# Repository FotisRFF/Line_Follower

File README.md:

##LINE FOLLOWER BODY 3D VIEW

##LINE FOLLOWER SENSOR 3D VIEW

#FRONT 

#BACK

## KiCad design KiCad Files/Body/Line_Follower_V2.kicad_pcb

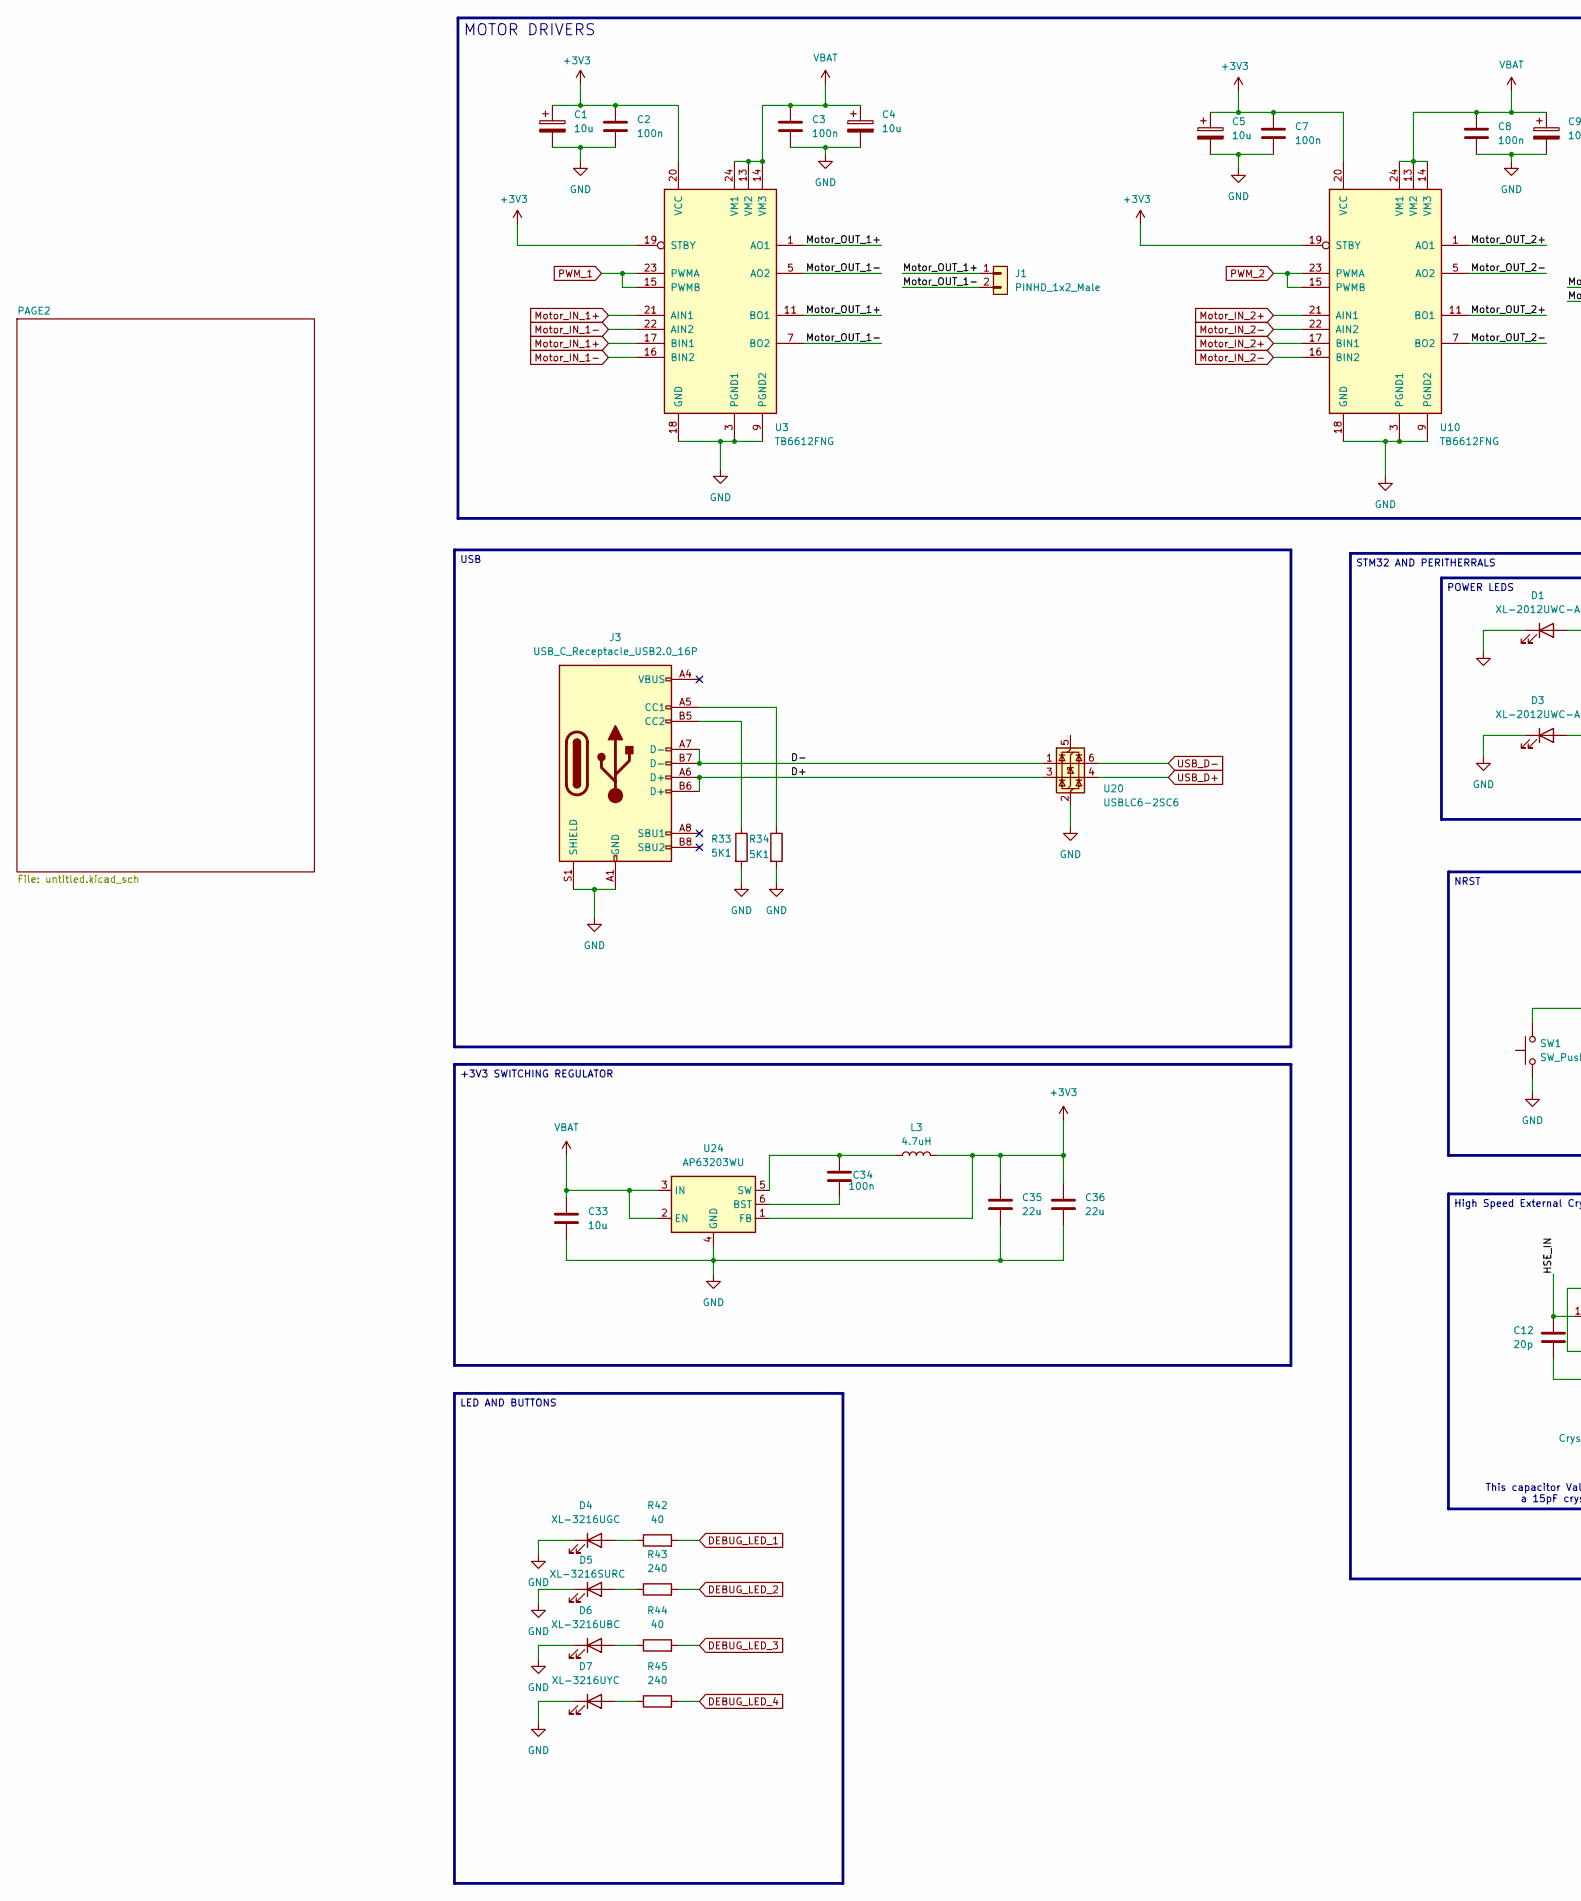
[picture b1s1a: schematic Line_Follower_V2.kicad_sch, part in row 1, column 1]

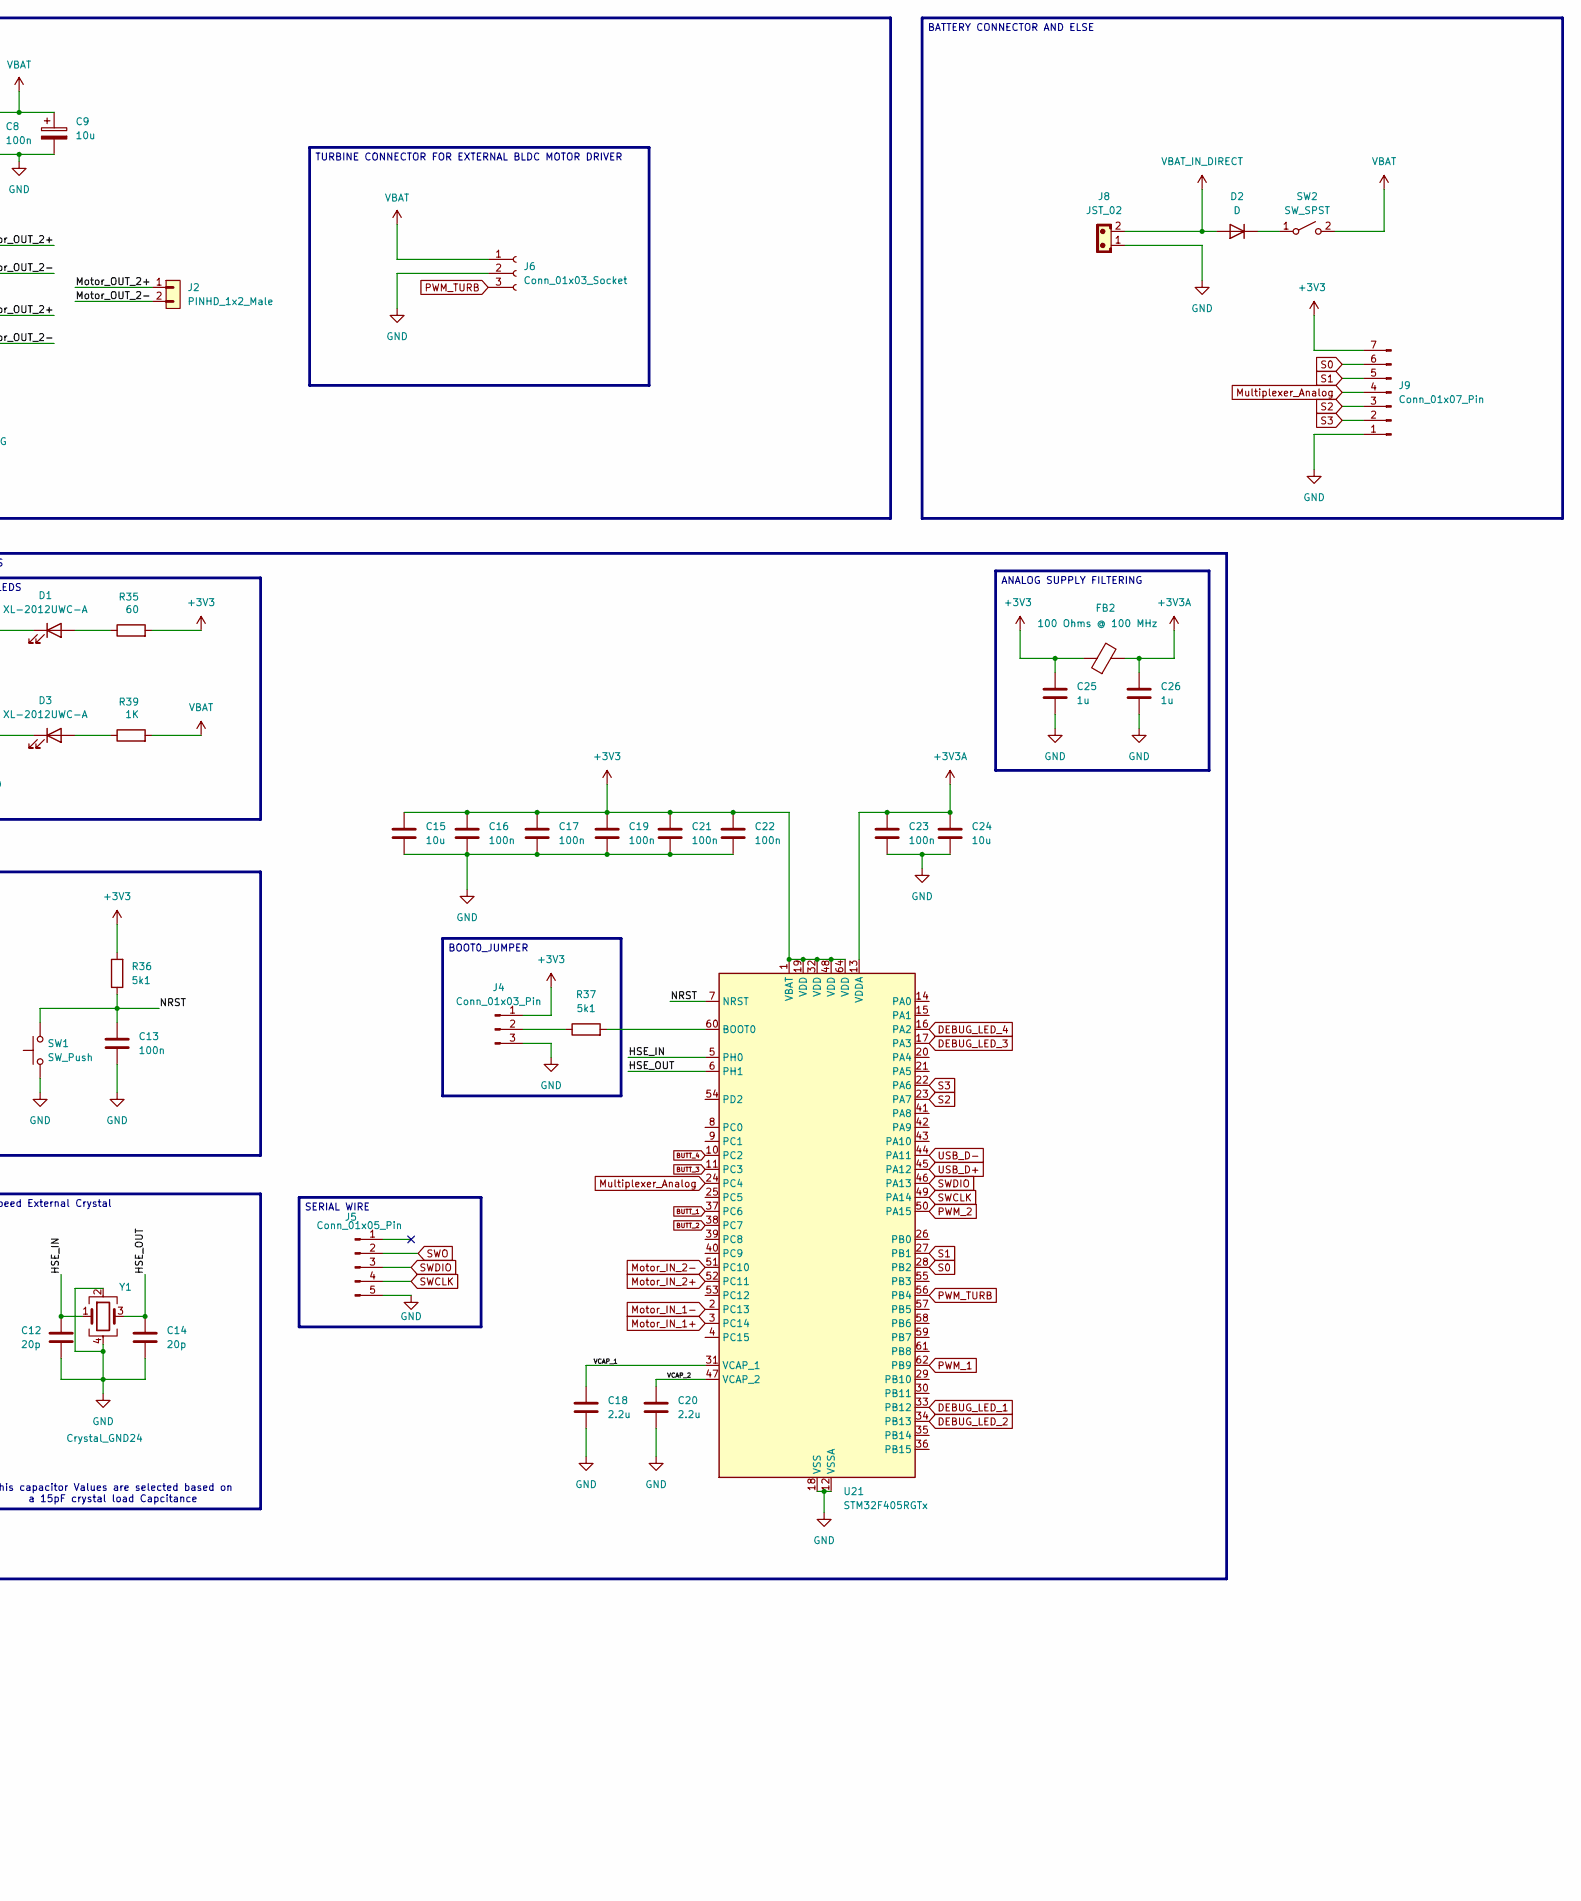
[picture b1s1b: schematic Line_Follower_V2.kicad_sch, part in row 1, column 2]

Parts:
C1, C4, C5, C9: 10u; CP_EIA-1608-08_AVX-J_HandSolder
C2, C3, C7, C8: 100n; C_0805_2012Metric
C12, C14: 20p; C_0402_1005Metric_Pad0.74x0.62mm_HandSolder
C13: 100n; C_0805_2012Metric_Pad1.18x1.45mm_HandSolder
C15, C24: 10u; C_0805_2012Metric_Pad1.18x1.45mm_HandSolder
C16, C17, C19, C21, C22, C23, C34: 100n; C_0402_1005Metric_Pad0.74x0.62mm_HandSolder
C18, C20: 2.2u; C_0603_1608Metric
C25, C26: 1u; C_0603_1608Metric
C33: 10u; C_0805_2012Metric
C35, C36: 22u; C_0805_2012Metric
D1, D3: XL-2012UWC-A; LED_0805_2012Metric_Pad1.15x1.40mm_HandSolder
D2: D; D_1206_3216Metric_Pad1.42x1.75mm_HandSolder
D4: XL-3216UGC; LED_1206_3216Metric
D5: XL-3216SURC; LED_1206_3216Metric
D6: XL-3216UBC; LED_1206_3216Metric
D7: XL-3216UYC; LED_1206_3216Metric
FB2: 100 Ohms @ 100 MHz; L_0805_2012Metric
J1, J2: PINHD_1x2_Male; PinHeader_1x02_P2.54mm_Vertical
J3: USB_C_Receptacle_USB2.0_16P; USB_C_Receptacle_GCT_USB4105-xx-A_16P_TopMnt_Horizontal
J4: Conn_01x03_Pin; PinHeader_1x03_P2.54mm_Vertical
J5: Conn_01x05_Pin; PinHeader_1x05_P2.54mm_Vertical
J6: Conn_01x03_Socket; PinHeader_1x03_P2.54mm_Vertical
J8: JST_02; JST_EH_B2B-EH-A_1x02_P2.50mm_Vertical
J9: Conn_01x07_Pin; PinHeader_1x07_P2.54mm_Vertical
L3: 4.7uH; L_Sunlord_MWSA0402S
R33, R34: 5K1; R_0805_2012Metric_Pad1.20x1.40mm_HandSolder
R35: 60; R_0805_2012Metric
R36, R37: 5k1; R_0805_2012Metric_Pad1.20x1.40mm_HandSolder
R39: 1K; R_0805_2012Metric
R42, R44: 40; R_0805_2012Metric_Pad1.20x1.40mm_HandSolder
R43, R45: 240; R_0805_2012Metric_Pad1.20x1.40mm_HandSolder
SW1: SW_Push; SW_PUSH_6mm_H13mm
SW2: SW_SPST; SW_DIP_SPSTx01_Slide_6.7x4.1mm_W7.62mm_P2.54mm_LowProfile
U3, U10: TB6612FNG; SSOP-24_5.3x8.2mm_P0.65mm
U20: USBLC6-2SC6; SOT-23-6
U21: STM32F405RGTx; LQFP-64_10x10mm_P0.5mm
U24: AP63203WU; TSOT-23-6
Y1: Crystal_GND24; Crystal_SMD_3225-4Pin_3.2x2.5mm

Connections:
+3V3: C1.1, C2.1, C5.1, C7.1, C15.1, C16.1, C17.1, C19.1, C21.1, C22.1, C25.1, C35.1, C36.1, FB2.1, J4.1, J9.7, L3.2, R35.2, R36.2, U3.19 (STBY), U3.20 (VCC), U10.19 (STBY), U10.20 (VCC), U21.1 (VBAT), U21.19 (VDD), U21.32 (VDD), U21.48 (VDD), U21.64 (VDD), U24.1 (FB)
+3V3A: C23.1, C24.1, C26.1, FB2.2, U21.13 (VDDA)
/D+: J3.A6 (D+), J3.B6 (D+), U20.3 (I/O2)
/D-: J3.A7 (D-), J3.B7 (D-), U20.1 (I/O1)
/HSE_IN: C12.1, U21.5 (PH0), Y1.1
/HSE_OUT: C14.1, U21.6 (PH1), Y1.3
/Motor_OUT_1+: J1.1, U3.1 (AO1), U3.2 (AO1), U3.11 (BO1), U3.12 (BO1)
/Motor_OUT_1-: J1.2, U3.5 (AO2), U3.6 (AO2), U3.7 (BO2), U3.8 (BO2)
/Motor_OUT_2+: J2.1, U10.1 (AO1), U10.2 (AO1), U10.11 (BO1), U10.12 (BO1)
/Motor_OUT_2-: J2.2, U10.5 (AO2), U10.6 (AO2), U10.7 (BO2), U10.8 (BO2)
/NRST: C13.1, R36.1, SW1.2, U21.7 (NRST)
/VCAP_1: C18.1, U21.31 (VCAP_1)
/VCAP_2: C20.1, U21.47 (VCAP_2)
BUTT_1: U21.37 (PC6)
BUTT_2: U21.38 (PC7)
BUTT_3: U21.11 (PC3)
BUTT_4: U21.10 (PC2)
DEBUG_LED_1: R42.2, U21.33 (PB12)
DEBUG_LED_2: R43.2, U21.34 (PB13)
DEBUG_LED_3: R44.2, U21.17 (PA3)
DEBUG_LED_4: R45.2, U21.16 (PA2)
GND: C1.2, C2.2, C3.2, C4.2, C5.2, C7.2, C8.2, C9.2, C12.2, C13.2, C14.2, C15.2, C16.2, C17.2, C18.2, C19.2, C20.2, C21.2, C22.2, C23.2, C24.2, C25.2, C26.2, C33.2, C35.2, C36.2, D1.1 (K), D3.1 (K), D4.1 (K), D5.1 (K), D6.1 (K), D7.1 (K), J3.A1 (GND), J3.A12 (GND), J3.B1 (GND), J3.B12 (GND), J3.S1 (SHIELD), J4.3, J5.5, J6.2, J8.1, J9.1, R33.2, R34.2, SW1.1, U3.3 (PGND1), U3.4 (PGND1), U3.9 (PGND2), U3.10 (PGND2), U3.18 (GND), U10.3 (PGND1), U10.4 (PGND1), U10.9 (PGND2), U10.10 (PGND2), U10.18 (GND), U20.2 (GND), U21.12 (VSSA), U21.18 (VSS), U21.63 (VSS), U24.4 (GND), Y1.2, Y1.4
Motor_IN_1+: U3.17 (BIN1), U3.21 (AIN1), U21.3 (PC14)
Motor_IN_1-: U3.16 (BIN2), U3.22 (AIN2), U21.2 (PC13)
Motor_IN_2+: U10.17 (BIN1), U10.21 (AIN1), U21.52 (PC11)
Motor_IN_2-: U10.16 (BIN2), U10.22 (AIN2), U21.51 (PC10)
Multiplexer_Analog: J9.4, U21.24 (PC4)
unnamed: D1.2 (A), R35.1
unnamed: D2.1 (K), SW2.1 (A)
unnamed: D3.2 (A), R39.1
unnamed: D4.2 (A), R42.1
unnamed: D5.2 (A), R43.1
unnamed: D6.2 (A), R44.1
unnamed: D7.2 (A), R45.1
unnamed: J3.A5 (CC1), R34.1
unnamed: J3.B5 (CC2), R33.1
unnamed: J4.2, R37.1
unnamed: R37.2, U21.60 (BOOT0)
unnamed: C34.2, U24.6 (BST)
unnamed: C34.1, L3.1, U24.5 (SW)
PWM_1: U3.15 (PWMB), U3.23 (PWMA), U21.62 (PB9)
PWM_2: U10.15 (PWMB), U10.23 (PWMA), U21.50 (PA15)
PWM_TURB: J6.3, U21.56 (PB4)
S0: J9.6, U21.28 (PB2)
S1: J9.5, U21.27 (PB1)
S2: J9.3, U21.23 (PA7)
S3: J9.2, U21.22 (PA6)
SWCLK: J5.4, U21.49 (PA14)
SWDIO: J5.3, U21.46 (PA13)
SWO: J5.2
USB_D+: U20.4 (I/O2), U21.45 (PA12)
USB_D-: U20.6 (I/O1), U21.44 (PA11)
VBAT: C3.1, C4.1, C8.1, C9.1, C33.1, J6.1, R39.2, SW2.2 (B), U3.13 (VM2), U3.14 (VM3), U3.24 (VM1), U10.13 (VM2), U10.14 (VM3), U10.24 (VM1), U24.2 (EN), U24.3 (IN)
VBAT_IN_DIRECT: D2.2 (A), J8.2

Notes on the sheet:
This capacitor Values are selected based on a 15pF crystal load Capcitance
LED AND BUTTONS
TURBINE CONNECTOR FOR EXTERNAL BLDC MOTOR DRIVER
ANALOG SUPPLY FILTERING
+3V3 SWITCHING REGULATOR
BATTERY CONNECTOR AND ELSE
High Speed External Crystal
POWER LEDS
MOTOR DRIVERS
BOOT0_JUMPER
NRST
STM32 AND PERITHERRALS
USB
SERIAL WIRE

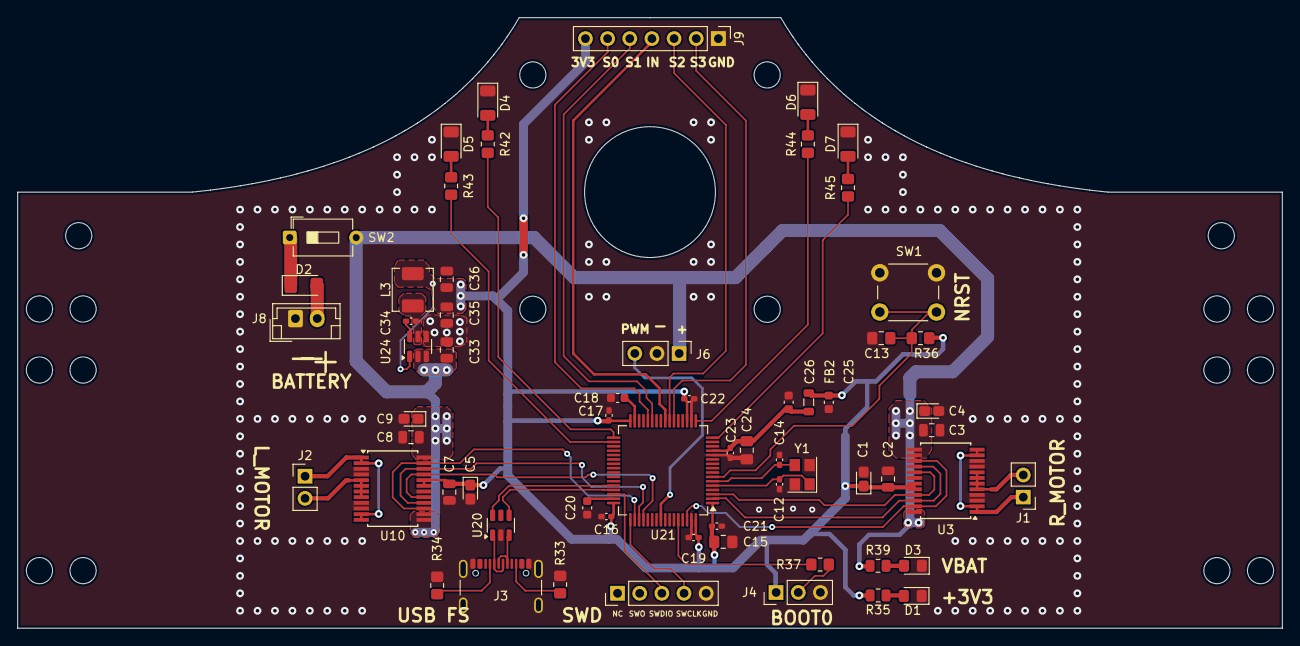
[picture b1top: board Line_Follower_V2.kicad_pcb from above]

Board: 2 copper layers, 145.0 x 70.0 mm, 62 parts (0 on the bottom side), 49 nets.

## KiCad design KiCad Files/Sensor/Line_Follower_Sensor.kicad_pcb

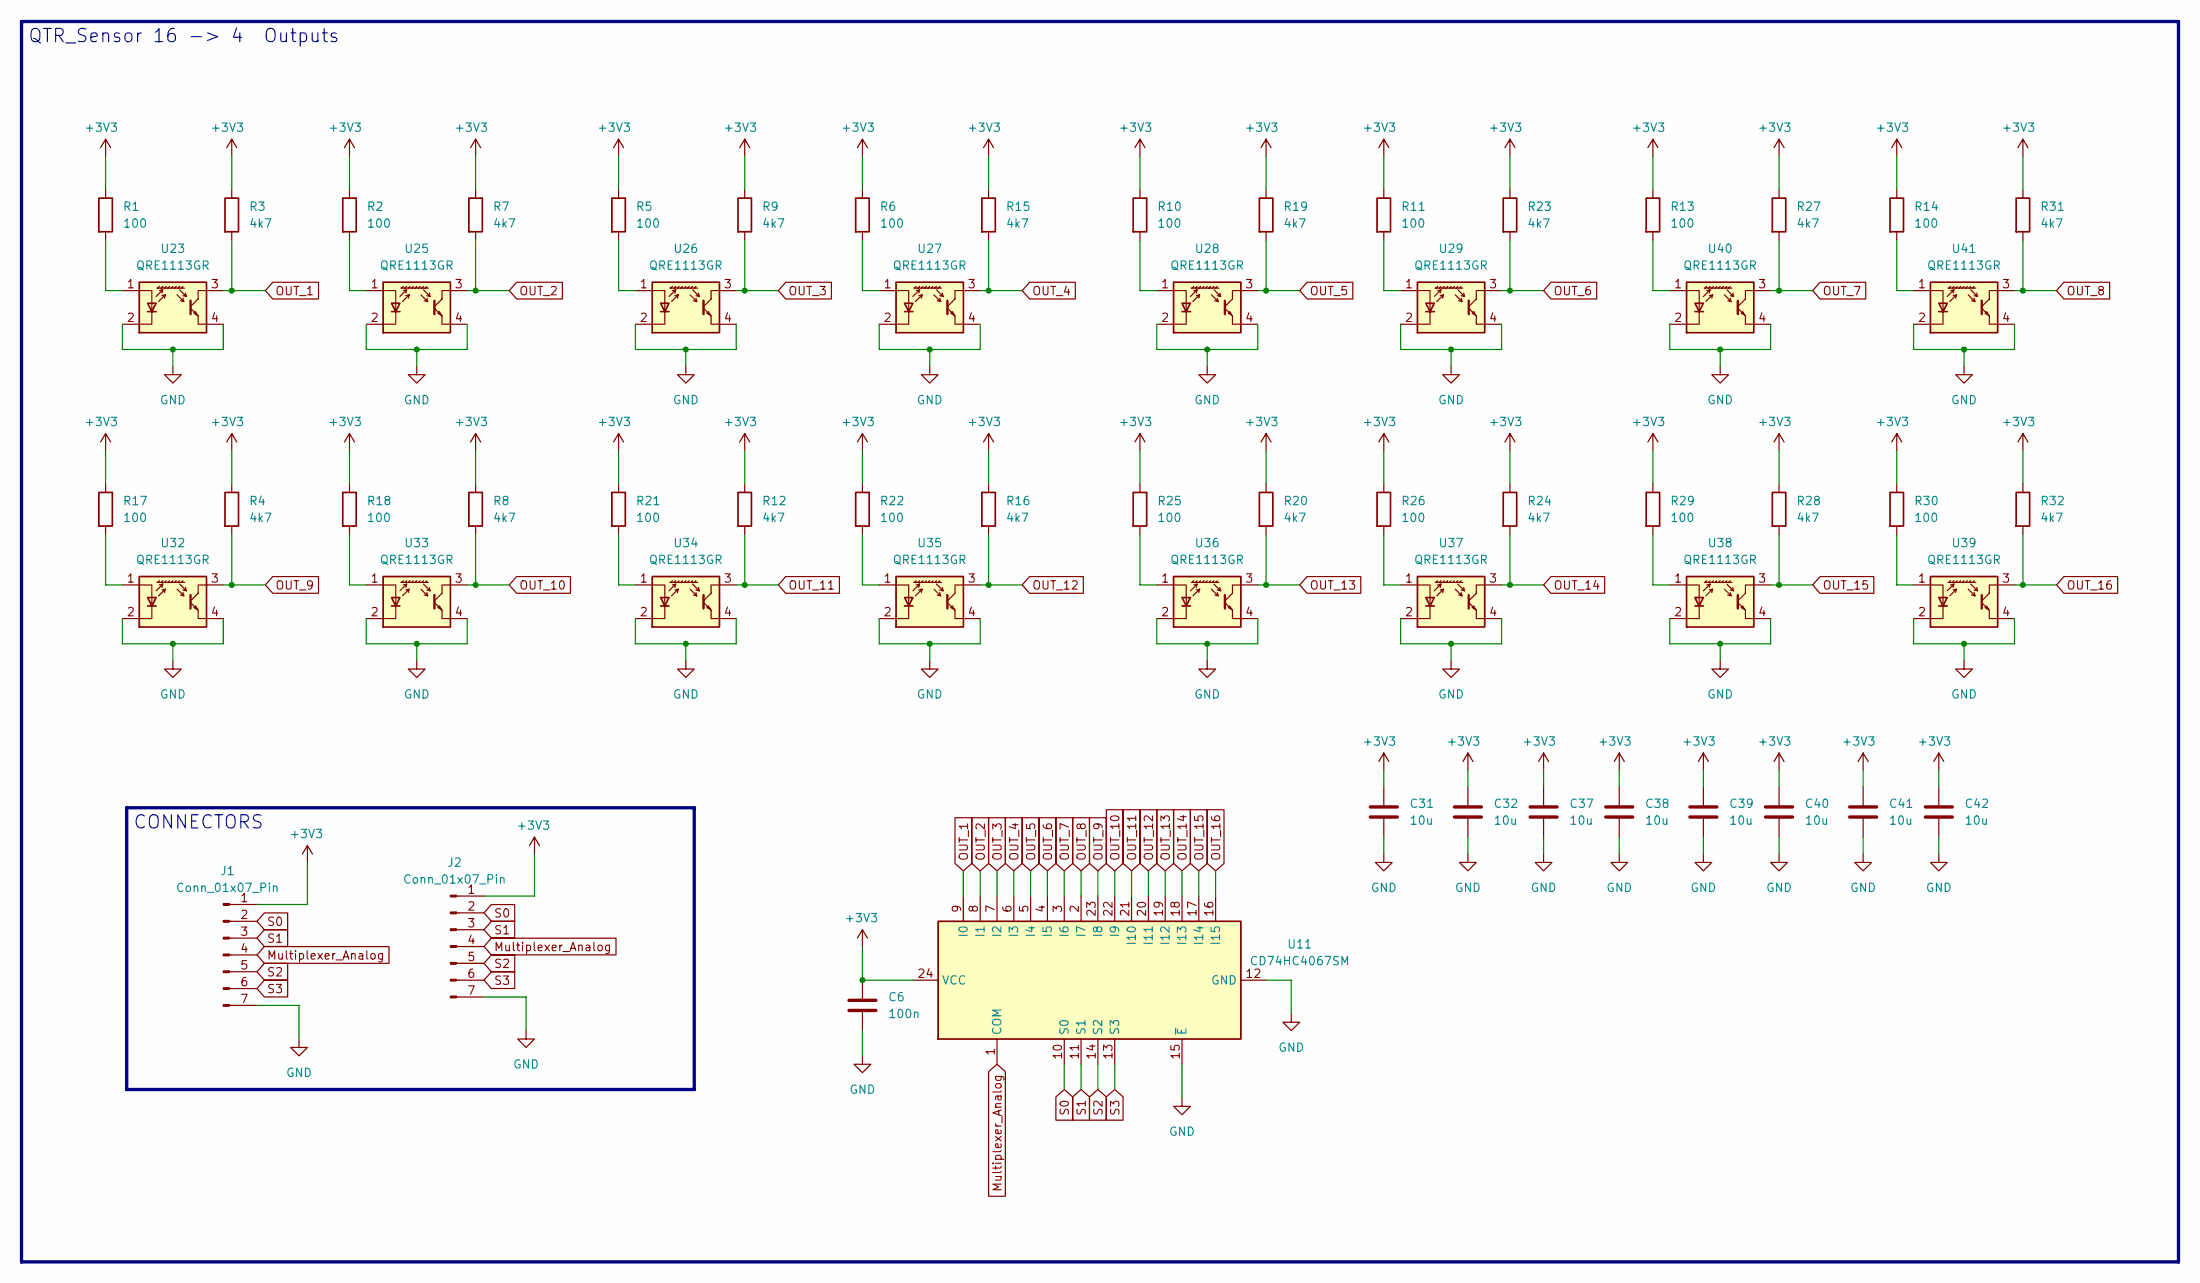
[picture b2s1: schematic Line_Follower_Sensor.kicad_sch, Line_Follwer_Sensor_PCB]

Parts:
C6: 100n; C_0402_1005Metric_Pad0.74x0.62mm_HandSolder
C31, C32, C37, C38, C39, C40, C41, C42: 10u; C_0805_2012Metric
J1, J2: Conn_01x07_Pin; PinHeader_1x07_P2.54mm_Vertical
R1, R2, R5, R6, R10, R11, R13, R14, R17, R18, R21, R22, R25, R26, R29, R30: 100; R_0603_1608Metric
R3, R4, R7, R8, R9, R12, R15, R16, R19, R20, R23, R24, R27, R28, R31, R32: 4k7; R_0603_1608Metric
U11: CD74HC4067SM; SSOP-24_5.3x8.2mm_P0.65mm
U23, U25, U26, U27, U28, U29, U32, U33, U34, U35, U36, U37, U38, U39, U40, U41: QRE1113GR; OnSemi_CASE100CY

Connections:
+3V3: C6.1, C31.1, C32.1, C37.1, C38.1, C39.1, C40.1, C41.1, C42.1, J1.1, J2.1, R1.1, R2.1, R3.1, R4.1, R5.1, R6.1, R7.1, R8.1, R9.1, R10.1, R11.1, R12.1, R13.1, R14.1, R15.1, R16.1, R17.1, R18.1, R19.1, R20.1, R21.1, R22.1, R23.1, R24.1, R25.1, R26.1, R27.1, R28.1, R29.1, R30.1, R31.1, R32.1, U11.24 (VCC)
GND: C6.2, C31.2, C32.2, C37.2, C38.2, C39.2, C40.2, C41.2, C42.2, J1.7, J2.7, U11.12 (GND), U11.15 (~E), U23.2 (K), U23.4, U25.2 (K), U25.4, U26.2 (K), U26.4, U27.2 (K), U27.4, U28.2 (K), U28.4, U29.2 (K), U29.4, U32.2 (K), U32.4, U33.2 (K), U33.4, U34.2 (K), U34.4, U35.2 (K), U35.4, U36.2 (K), U36.4, U37.2 (K), U37.4, U38.2 (K), U38.4, U39.2 (K), U39.4, U40.2 (K), U40.4, U41.2 (K), U41.4
Multiplexer_Analog: J1.4, J2.4, U11.1 (COM)
unnamed: R1.2, U23.1 (A)
unnamed: R2.2, U25.1 (A)
unnamed: R5.2, U26.1 (A)
unnamed: R6.2, U27.1 (A)
unnamed: R10.2, U28.1 (A)
unnamed: R11.2, U29.1 (A)
unnamed: R17.2, U32.1 (A)
unnamed: R18.2, U33.1 (A)
unnamed: R21.2, U34.1 (A)
unnamed: R22.2, U35.1 (A)
unnamed: R25.2, U36.1 (A)
unnamed: R26.2, U37.1 (A)
unnamed: R29.2, U38.1 (A)
unnamed: R30.2, U39.1 (A)
unnamed: R13.2, U40.1 (A)
unnamed: R14.2, U41.1 (A)
OUT_1: R3.2, U11.9 (I0), U23.3
OUT_2: R7.2, U11.8 (I1), U25.3
OUT_3: R9.2, U11.7 (I2), U26.3
OUT_4: R15.2, U11.6 (I3), U27.3
OUT_5: R19.2, U11.5 (I4), U28.3
OUT_6: R23.2, U11.4 (I5), U29.3
OUT_7: R27.2, U11.3 (I6), U40.3
OUT_8: R31.2, U11.2 (I7), U41.3
OUT_9: R4.2, U11.23 (I8), U32.3
OUT_10: R8.2, U11.22 (I9), U33.3
OUT_11: R12.2, U11.21 (I10), U34.3
OUT_12: R16.2, U11.20 (I11), U35.3
OUT_13: R20.2, U11.19 (I12), U36.3
OUT_14: R24.2, U11.18 (I13), U37.3
OUT_15: R28.2, U11.17 (I14), U38.3
OUT_16: R32.2, U11.16 (I15), U39.3
S0: J1.2, J2.2, U11.10 (S0)
S1: J1.3, J2.3, U11.11 (S1)
S2: J1.5, J2.5, U11.14 (S2)
S3: J1.6, J2.6, U11.13 (S3)

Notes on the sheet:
CONNECTORS
QTR_Sensor 16 -> 4 Outputs

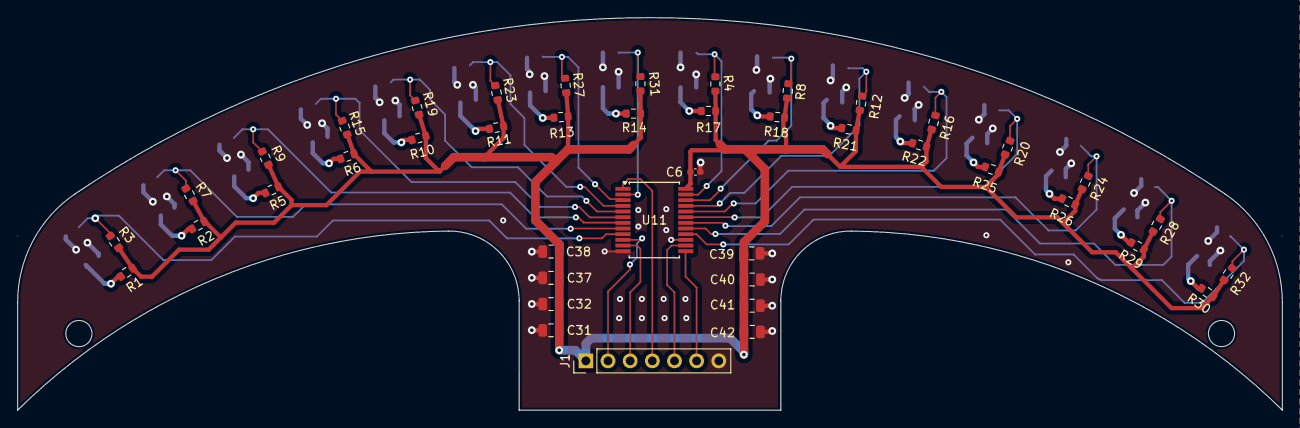
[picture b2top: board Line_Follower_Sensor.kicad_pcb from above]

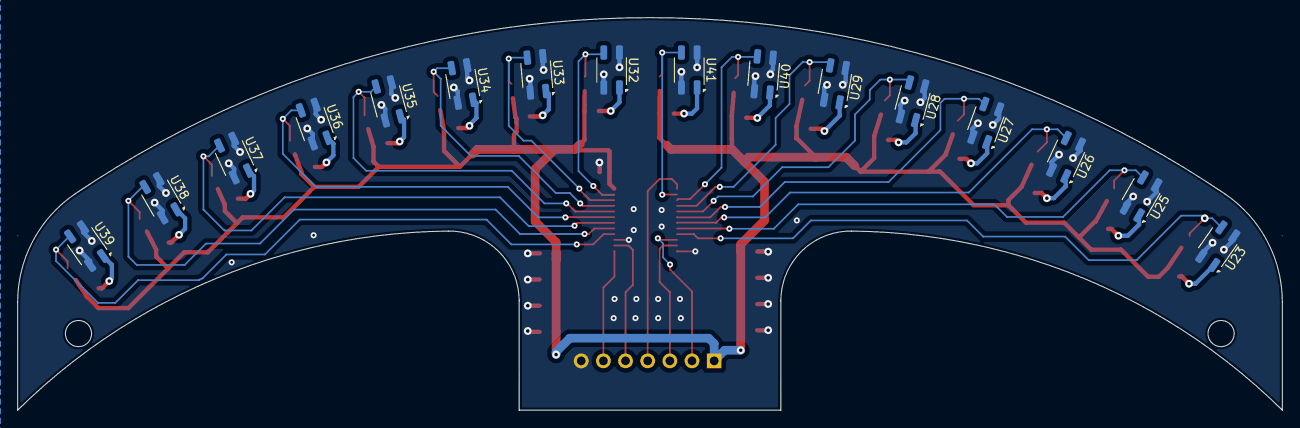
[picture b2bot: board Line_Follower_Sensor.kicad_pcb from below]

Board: 2 copper layers, 145.0 x 45.0 mm, 59 parts (16 on the bottom side), 39 nets.

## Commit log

2025-12-01 Create testy
2025-12-01 Create test
